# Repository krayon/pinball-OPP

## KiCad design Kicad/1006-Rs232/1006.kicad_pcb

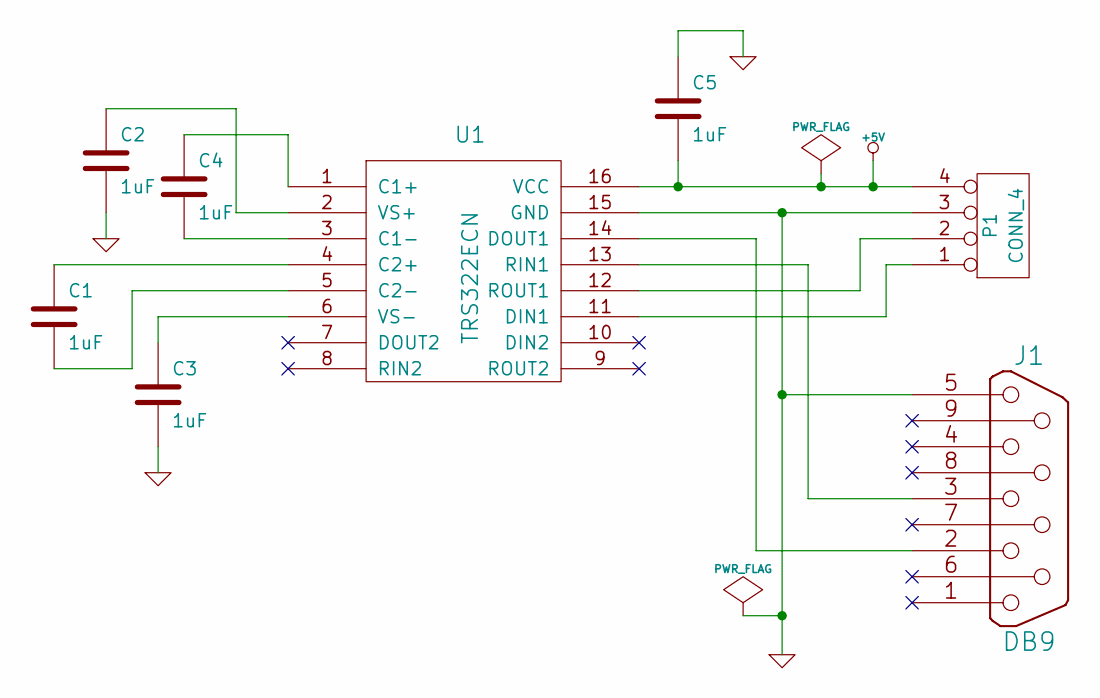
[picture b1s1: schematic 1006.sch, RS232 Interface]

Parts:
C1, C2, C3, C4, C5: 1uF
J1: DB9
P1: CONN_4
U1: TRS322ECN

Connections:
+5V: C5.2, P1.4, U1.16 (VCC)
GND: C2.2, C3.2, C5.1, J1.5, P1.3, U1.15 (GND)
unnamed: C3.1, U1.6 (VS-)
unnamed: P1.1, U1.11 (DIN1)
unnamed: J1.2, U1.14 (DOUT1)
unnamed: J1.3, U1.13 (RIN1)
unnamed: P1.2, U1.12 (ROUT1)
unnamed: C1.2, U1.5 (C2-)
unnamed: C1.1, U1.4 (C2+)
unnamed: C2.1, U1.2 (VS+)
unnamed: C4.2, U1.3 (C1-)
unnamed: C4.1, U1.1 (C1+)

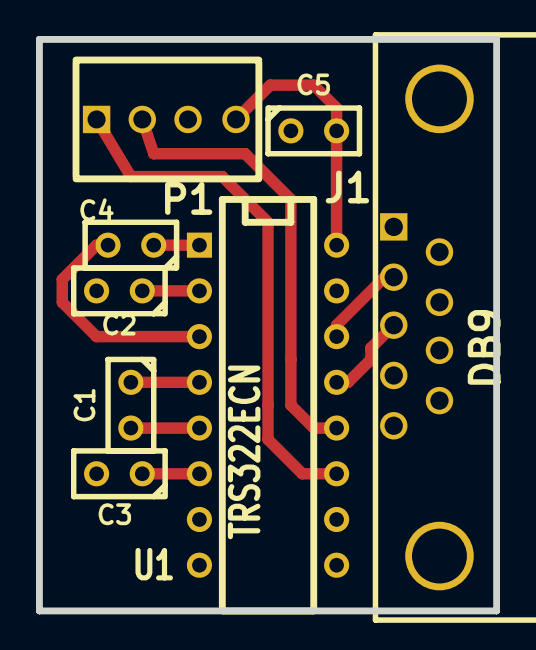
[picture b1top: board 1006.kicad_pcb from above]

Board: 2 copper layers, 25.4 x 31.8 mm, 8 parts (0 on the bottom side), 12 nets.

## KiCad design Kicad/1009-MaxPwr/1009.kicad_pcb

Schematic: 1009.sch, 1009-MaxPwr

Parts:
P1, P2, P3, P4, P5, P6, P9, P10, P14, P18, P22: SPADE_187
P7, P12, P16, P20: CONN2X3PCP6MB
P8, P13, P17, P21: CONN2X12PCPWR
P11, P15, P19, P23: CONN_2
P24: CONN2X12
P25, P26, P27, P28: TST
R1, R2, R3: 100K

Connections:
3.3V: P8.1, P8.2, P8.13, P10.1, P10.2, P24.17, P24.18
5V: P6.1, P6.2, P8.22, P8.23
5VSTBY: P5.1, P5.2, P8.9, P24.4
5V_1: P8.4, P8.6, P24.5
12V: P7.4, P7.5, P7.6, P12.1, P12.2, P12.3, P24.6
12V_1: P8.10, P8.11, P9.1, P9.2, P13.18, P13.19, P13.24, R1.2, R2.1
24V: P12.4, P12.5, P12.6, P16.1, P16.2, P16.3, P24.3, P24.15
24V_1: P13.10, P13.11, P14.1, P14.2, P17.18, P17.19, P17.24, R2.2, R3.1
36V: P16.4, P16.5, P16.6, P20.1, P20.2, P20.3
36V_1: P17.10, P17.11, P18.1, P18.2, P21.18, P21.19, P21.24, R3.2
48V: P20.4, P20.5, P20.6, P21.10, P21.11, P22.1, P22.2, P24.1, P24.2, P24.13, P24.14
GND: P1.1, P1.2, P2.1, P2.2, P3.1, P3.2, P4.1, P4.2, P7.1, P7.2, P7.3, P8.3, P8.5, P8.7, P8.15, P8.17, P8.18, P8.19, P8.24, P11.2 (PM), P24.7, P24.8, P24.9, P24.10, P24.11, P24.12, P24.19, P24.20, P24.21, P24.22, P24.23, P24.24, R1.1
unnamed: P21.15, P23.2 (PM)
unnamed: P13.16, P15.1
unnamed: P17.16, P19.1
unnamed: P21.16, P23.1
unnamed: P17.15, P19.2 (PM)
unnamed: P13.15, P15.2 (PM)
PS_ON*: P8.16, P11.1, P24.16

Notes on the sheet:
3.3V

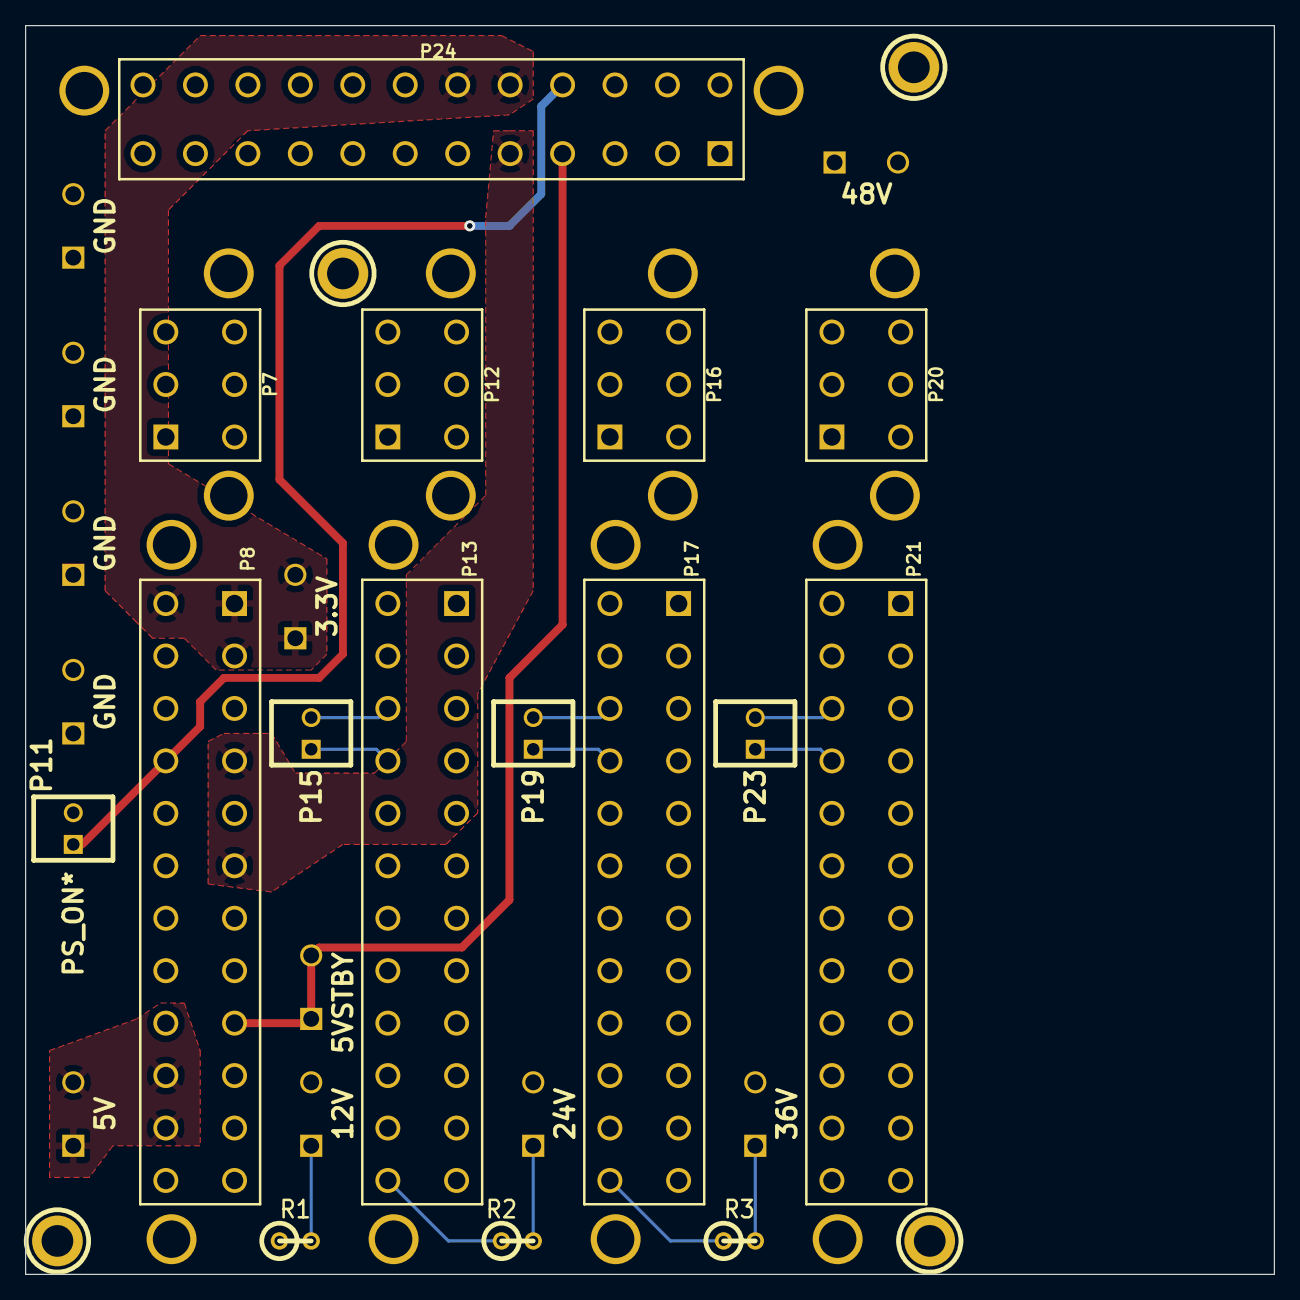
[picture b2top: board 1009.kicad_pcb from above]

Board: 2 copper layers, 100.0 x 100.0 mm, 31 parts (0 on the bottom side), 19 nets.

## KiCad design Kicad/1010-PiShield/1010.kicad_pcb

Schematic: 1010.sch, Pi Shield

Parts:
C1: .1uF
K1: CONN_3
P1: CONN2X13
P2, P3: CONN_4
P4, P8, P10, P11: TST
P5, P6, P7: SPADE_187
P9: CONN_2
Q1: MOSFET_N
R1: 10K
U1: 74LVC245A

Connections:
3.3V: C1.1, P1.1, U1.1 (DIR), U1.20 (VCC)
3.3V_1: K1.3, P6.1, P6.2
5V: P1.2, P2.1, P5.1, P5.2
CS0: P1.24, U1.5 (A4)
GND: C1.2, P1.6, P1.9, P1.14, P1.20, P1.25, P2.2, P4.1, P7.1, P7.2, P8.1, P9.2 (PM), P10.1, Q1.S, R1.2, U1.10 (GND), U1.19 (OE*)
GPIO7: P1.26, U1.8 (A7)
GPIO18: P1.12, U1.7 (A6)
GPIO25: P1.22, U1.9 (A8)
MOSI: P1.19, U1.4 (A3)
unnamed: Q1.G, R1.1, U1.13 (B6)
unnamed: P3.2, U1.15 (B4)
unnamed: K1.2 (PM), P3.4
unnamed: P2.3, U1.18 (B1)
unnamed: P2.4, U1.3 (A2)
unnamed: P3.1, U1.16 (B3)
unnamed: K1.1, U1.11 (B8)
unnamed: P3.3, U1.14 (B5)
PS_ON*: P9.1, Q1.D
RxD: P1.10, U1.17 (B2)
SCLK: P1.23, U1.6 (A5)
TxD: P1.8, U1.2 (A1)

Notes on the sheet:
LED Drv
Sol/Inp Cards
3.3V or OE* to LED drv

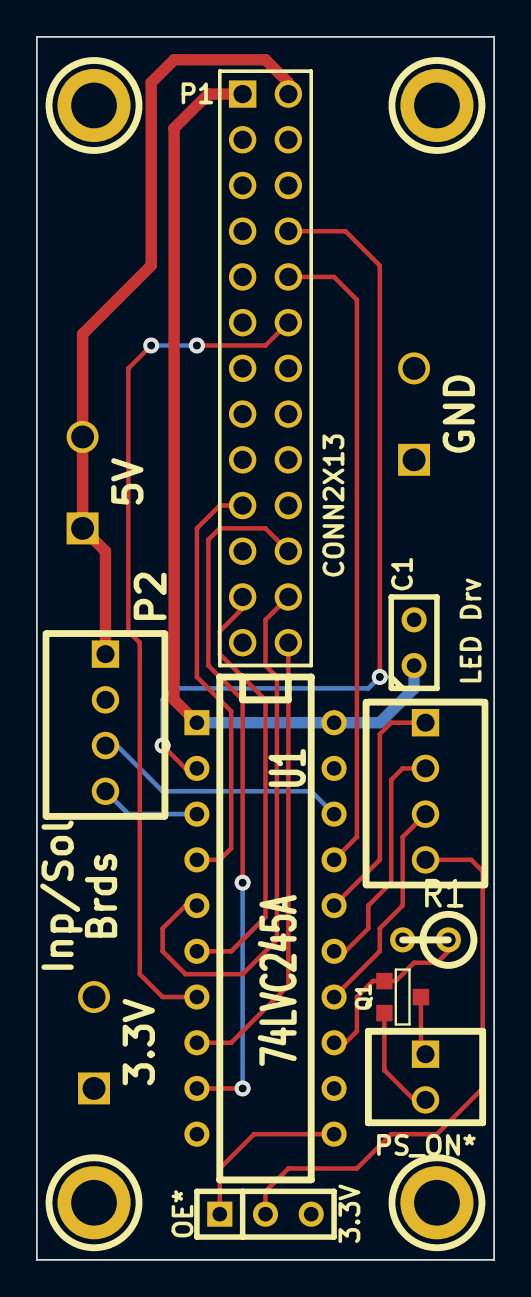
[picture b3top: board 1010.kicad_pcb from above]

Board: 2 copper layers, 25.4 x 67.9 mm, 16 parts (0 on the bottom side), 21 nets.

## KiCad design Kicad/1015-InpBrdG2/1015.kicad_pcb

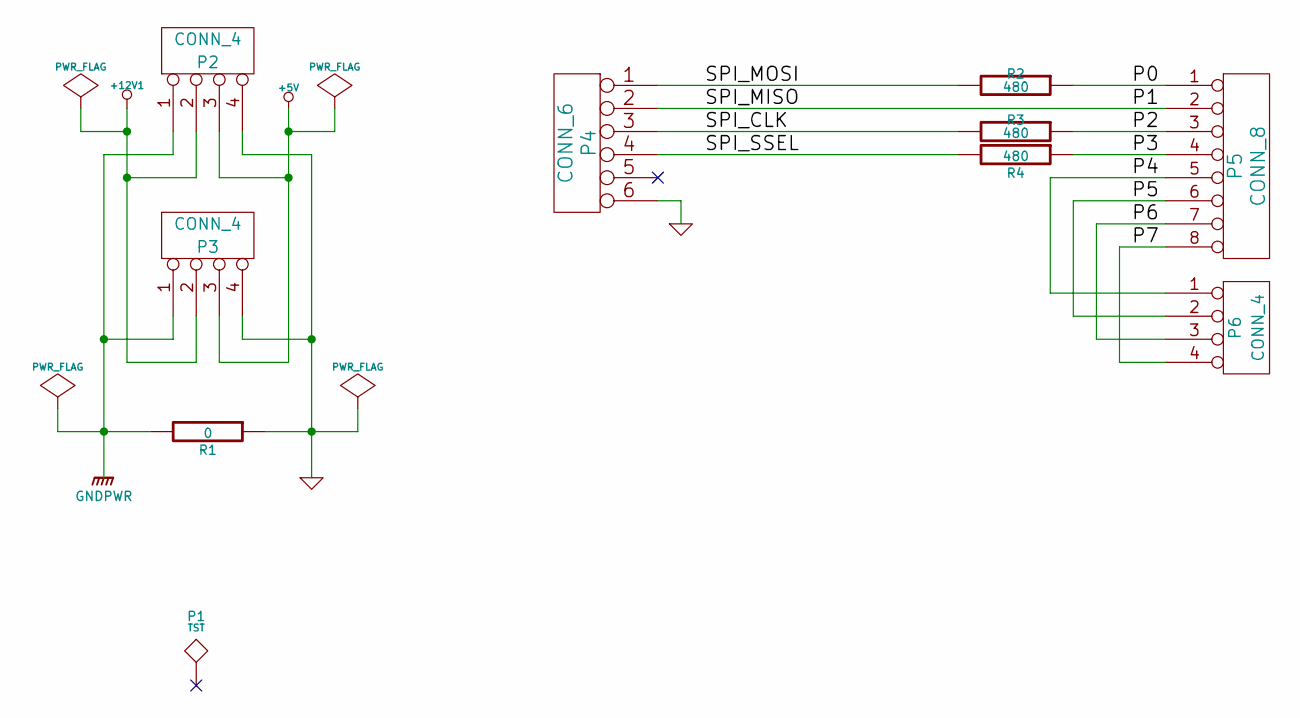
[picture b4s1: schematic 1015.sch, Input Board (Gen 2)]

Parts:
P1: TST
P2, P3, P6: CONN_4; Manufacturer PN 68001-436HLF
P4: CONN_6
P5: CONN_8
R1: 0
R2, R3, R4: 480

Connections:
+5V: P2.3, P3.3
+12V1: P2.2, P3.2
/P0: P5.1, R2.1
/P1: P4.2, P5.2
/P2: P5.3, R3.1
/P3: P5.4, R4.1
/P4: P5.5, P6.1
/P5: P5.6, P6.2
/P6: P5.7, P6.3
/P7: P5.8, P6.4
/SPI_CLK: P4.3, R3.2
/SPI_MOSI: P4.1, R2.2
/SPI_SSEL: P4.4, R4.2
GND: P2.4, P3.4, P4.6, R1.1
GNDPWR: P2.1, P3.1, R1.2

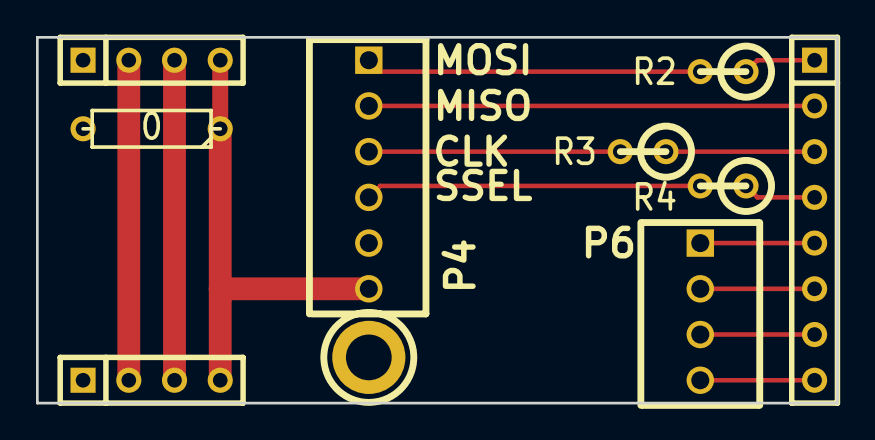
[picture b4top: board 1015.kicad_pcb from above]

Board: 2 copper layers, 44.5 x 20.3 mm, 11 parts (0 on the bottom side), 15 nets.

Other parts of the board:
VAL: REF; opp_logo_backsilk
